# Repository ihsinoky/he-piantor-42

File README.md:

# HE Piantor 42

42-key Hall-effect keyboard targeting a unified reverse-V assembly. D-015
defines reusable Main + Left/Right Wings; future Wing geometry must be
project-owned or explicitly approved.

> [!WARNING]
> **Experimental hardware:** Main Rev.4, Matrix Rev.3, Wing Rev.3 and the final
> case data are design baselines. No PCB has completed physical validation,
> and this repository does
> not describe a production-ready keyboard. Do not order or manufacture from
> the current files without completing the documented review gates.

## Target

- 42 keys
- Piantor-derived column-staggered layout
- Unified reverse-V keyboard assembly; modular Main + Wings
- Evaluate 17.0 / 16.5 / 16.0 mm pitch; production pitch remains open
- Full-height Hall-effect magnetic switches
- USB-C wired only
- Vial-compatible keymap, 4 layers
- Dedicated power indicator LED
- Separate layer indicator LED
- JLCPCB PCBA target
- FDM-printable enclosure

## Development flow

The design baseline is Main Rev.4 / Matrix Rev.3 / Wing Rev.3 / final case data.
Start with the [current artifacts index](docs/artifacts-index.md) for CAD,
manufacturing packages, case exports and recorded verification.
[Project status](docs/project-status.md) is authoritative for outstanding gates:
Order 1 awaits PO GO, production pitch awaits Matrix measurements, and physical
validation is pending. The [dashboard](task/index.html) shows the milestone plan
and current position as a non-authoritative read model.

## Contribution status

Public release is completed, as recorded in
[`docs/public-release-readiness.md`](docs/public-release-readiness.md).
JITX physical-backend evaluation concluded NO-GO (D-016); it is historical,
not an unresolved current design gate. Prospective contributors should start
with an Issue and follow
[`docs/development-workflow.md`](docs/development-workflow.md); a green CI run
does not replace Product Owner approval.

## Licensing

This is a mixed-license repository:

- project-authored hardware, mechanical, and manufacturing designs use
  CERN-OHL-P-2.0;
- project-authored firmware, software, scripts, dashboard, and documentation
  use the MIT License; and
- third-party files retain their original licenses and notices.

See the authoritative [`LICENSE.md`](LICENSE.md) path map, the full texts under
[`LICENSES/`](LICENSES/), and the canonical
[third-party inventory](hardware/lib/THIRD_PARTY.md). Items marked **REVIEW
REQUIRED** are public-release blockers, not an assertion of ownership.

Public-release audit evidence and the current Human Gate result are documented
in [`docs/public-release-readiness.md`](docs/public-release-readiness.md). This
repository has completed public release; the hardware remains experimental and
is not production-ready.

設計の世代・過去の試行・証跡は [履歴索引](docs/history-index.md) を参照。

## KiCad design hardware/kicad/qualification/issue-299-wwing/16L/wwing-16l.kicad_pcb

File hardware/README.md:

# Hardware

現行は Main Rev.4／Matrix Rev.3／Wing Rev.3。CAD・回路源、単板とパネル、
ケース入力CSVは [成果物索引](../docs/artifacts-index.md) から正本へ進んでください。
Main は UDB C3 を別基板に持ち、左右Wingへ各200mmのハーネスで接続します。
Matrix は評価用18キー基板で、製品Wingとは別です。

設計採択と実機合格・発注GOは別です。[現行状態と残件](../docs/project-status.md)を参照。
`sensor-test/`、`main/`、旧Rev.M1やEDA評価の資料は設計履歴を含みます。

設計の世代・過去の試行・証跡は [履歴索引](../docs/history-index.md) を参照。

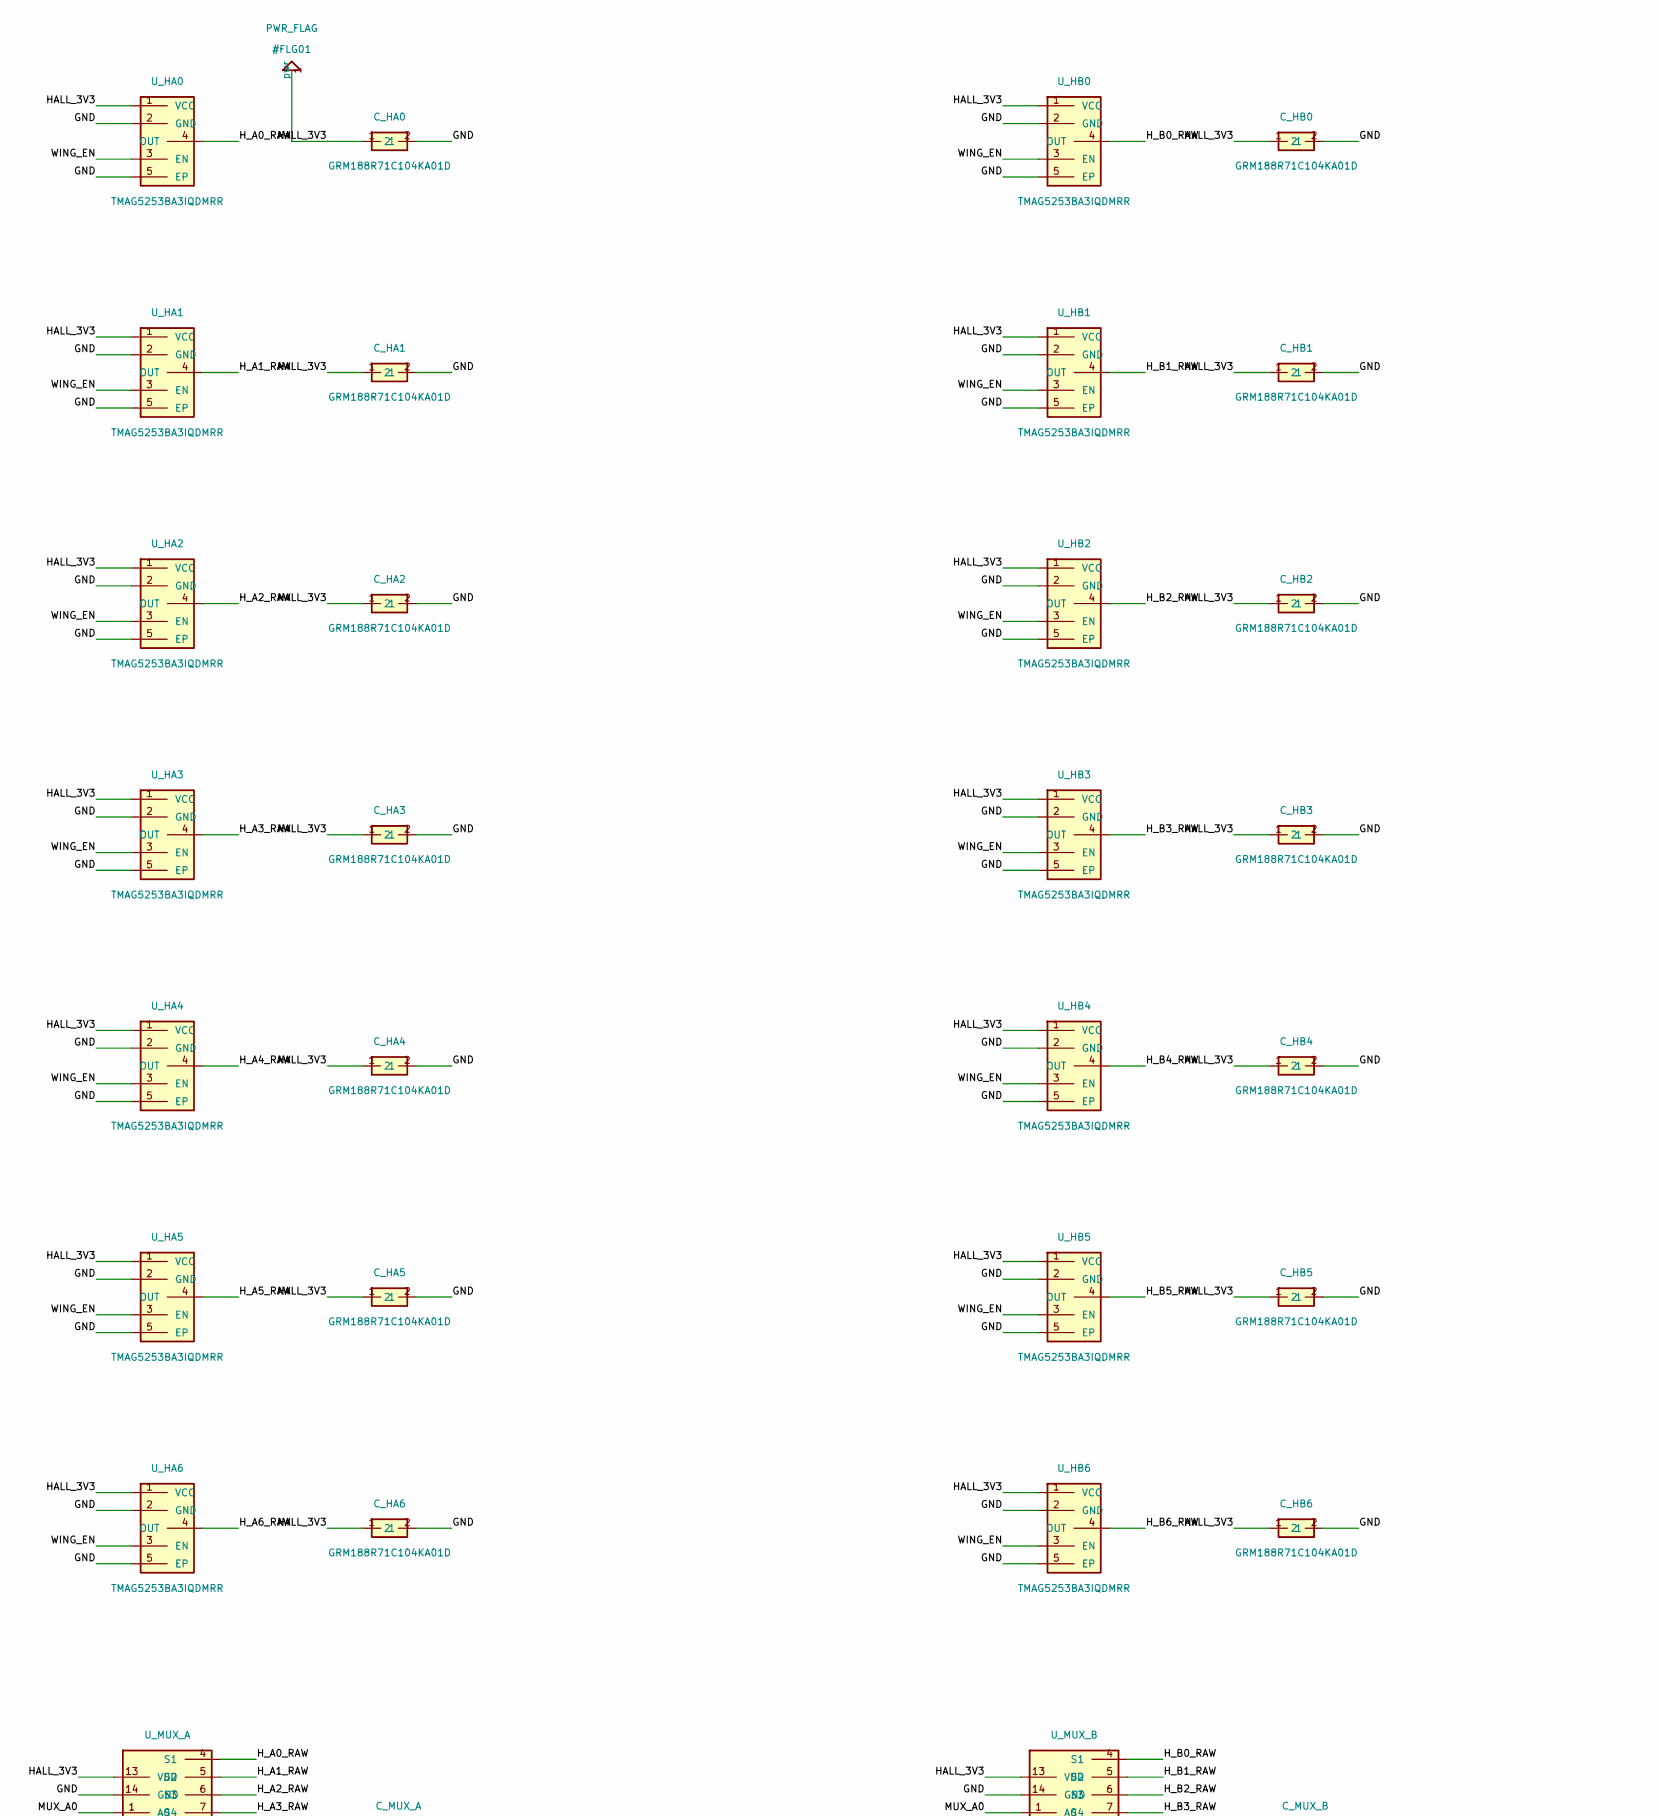
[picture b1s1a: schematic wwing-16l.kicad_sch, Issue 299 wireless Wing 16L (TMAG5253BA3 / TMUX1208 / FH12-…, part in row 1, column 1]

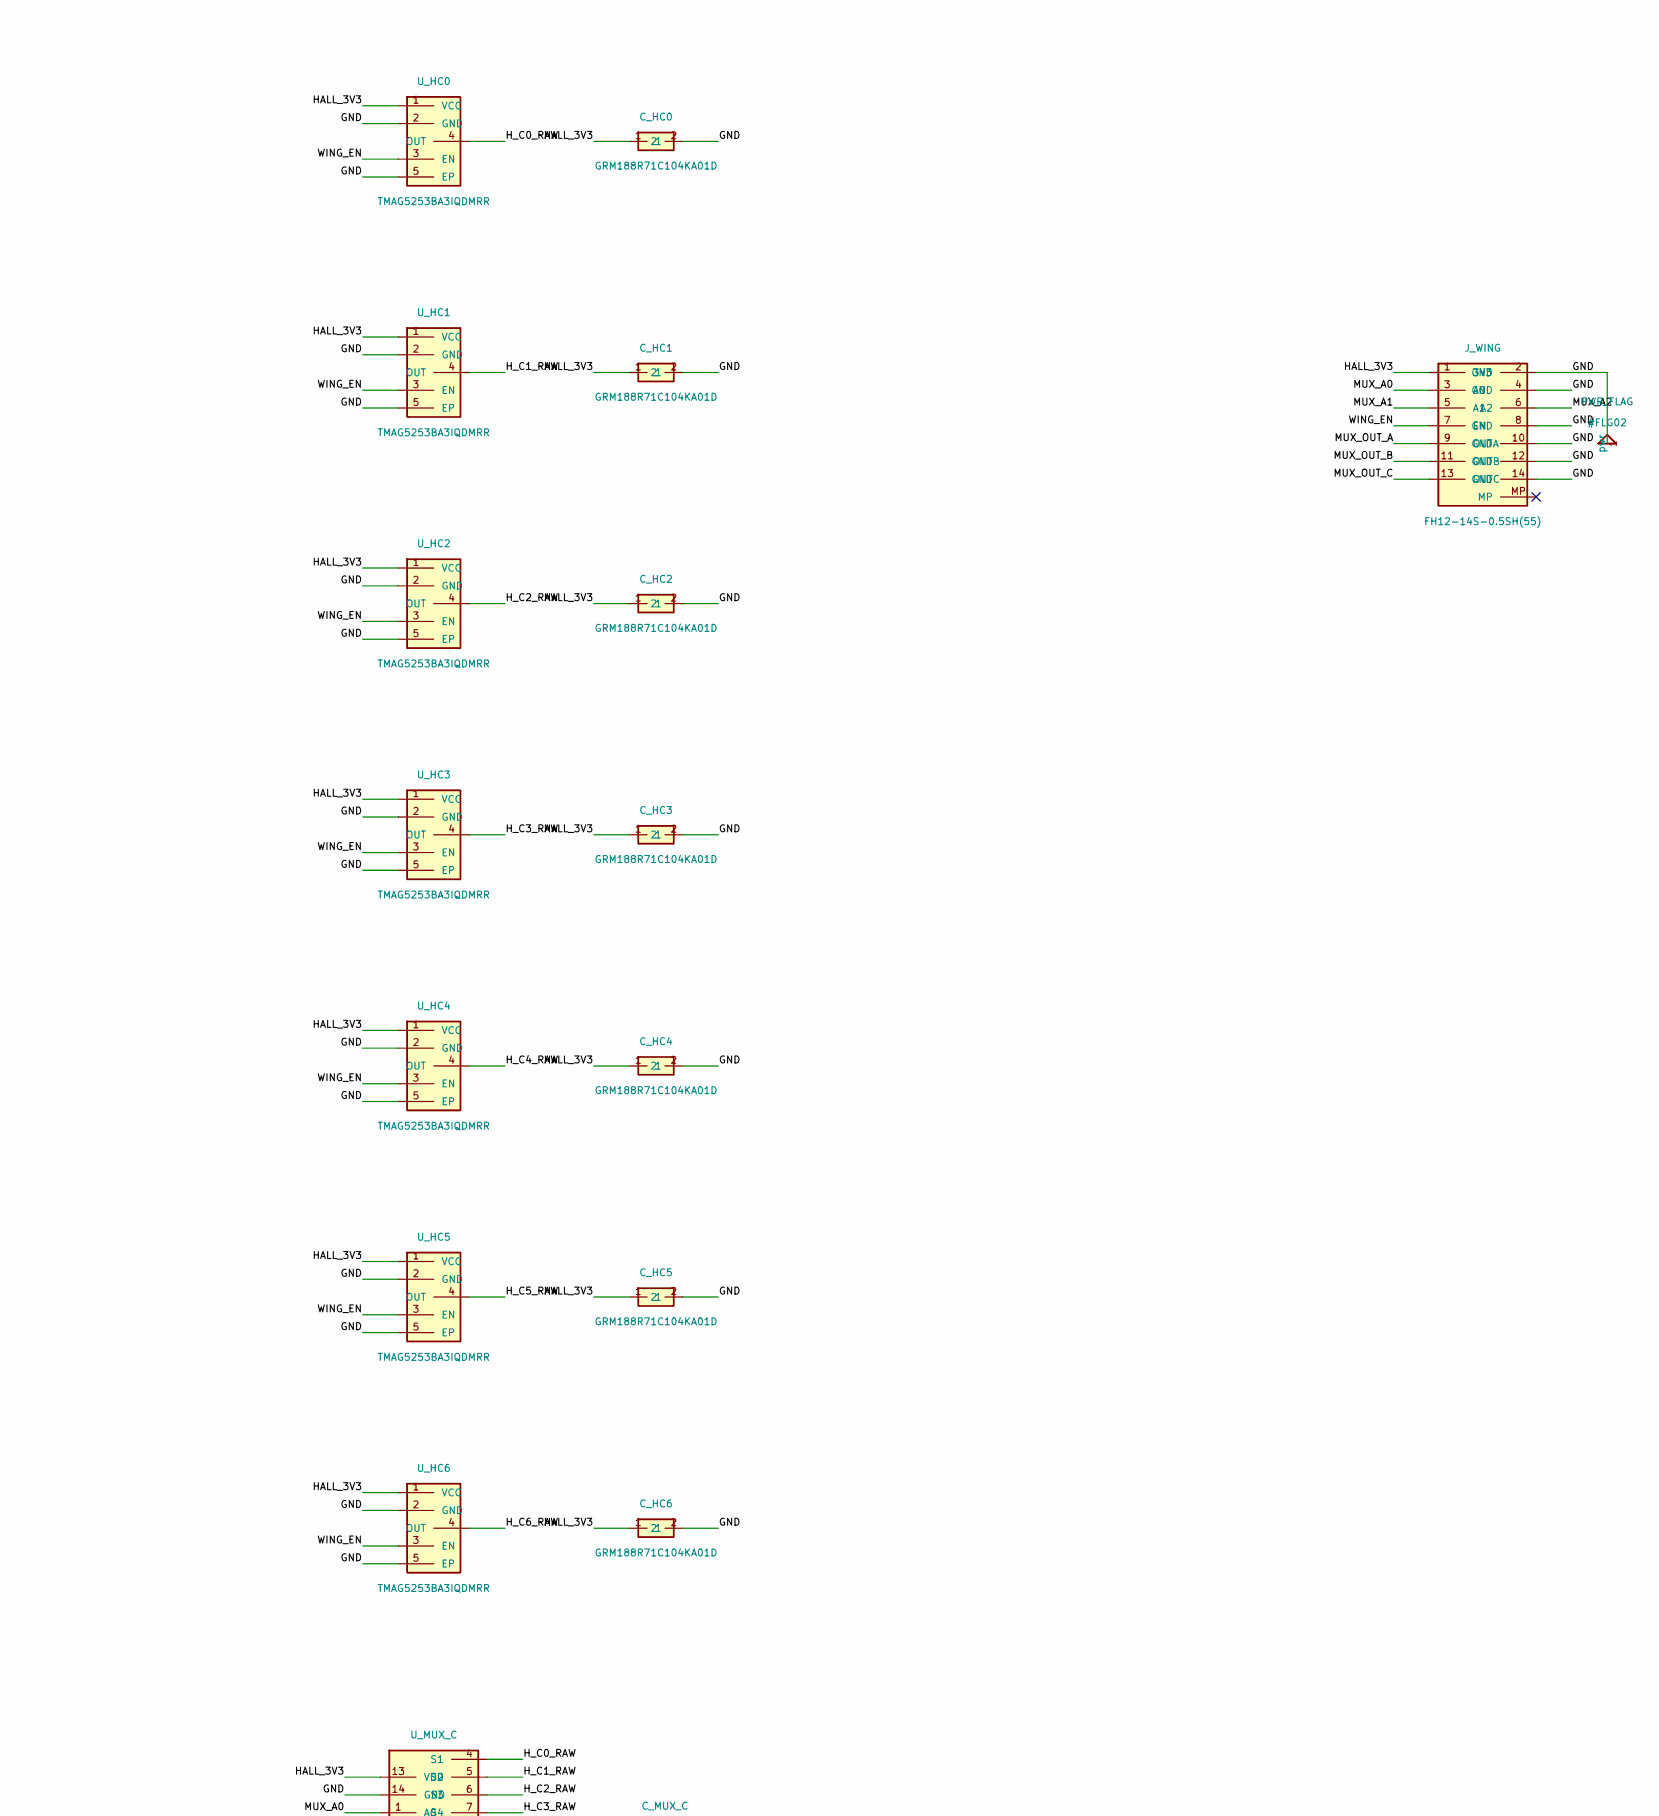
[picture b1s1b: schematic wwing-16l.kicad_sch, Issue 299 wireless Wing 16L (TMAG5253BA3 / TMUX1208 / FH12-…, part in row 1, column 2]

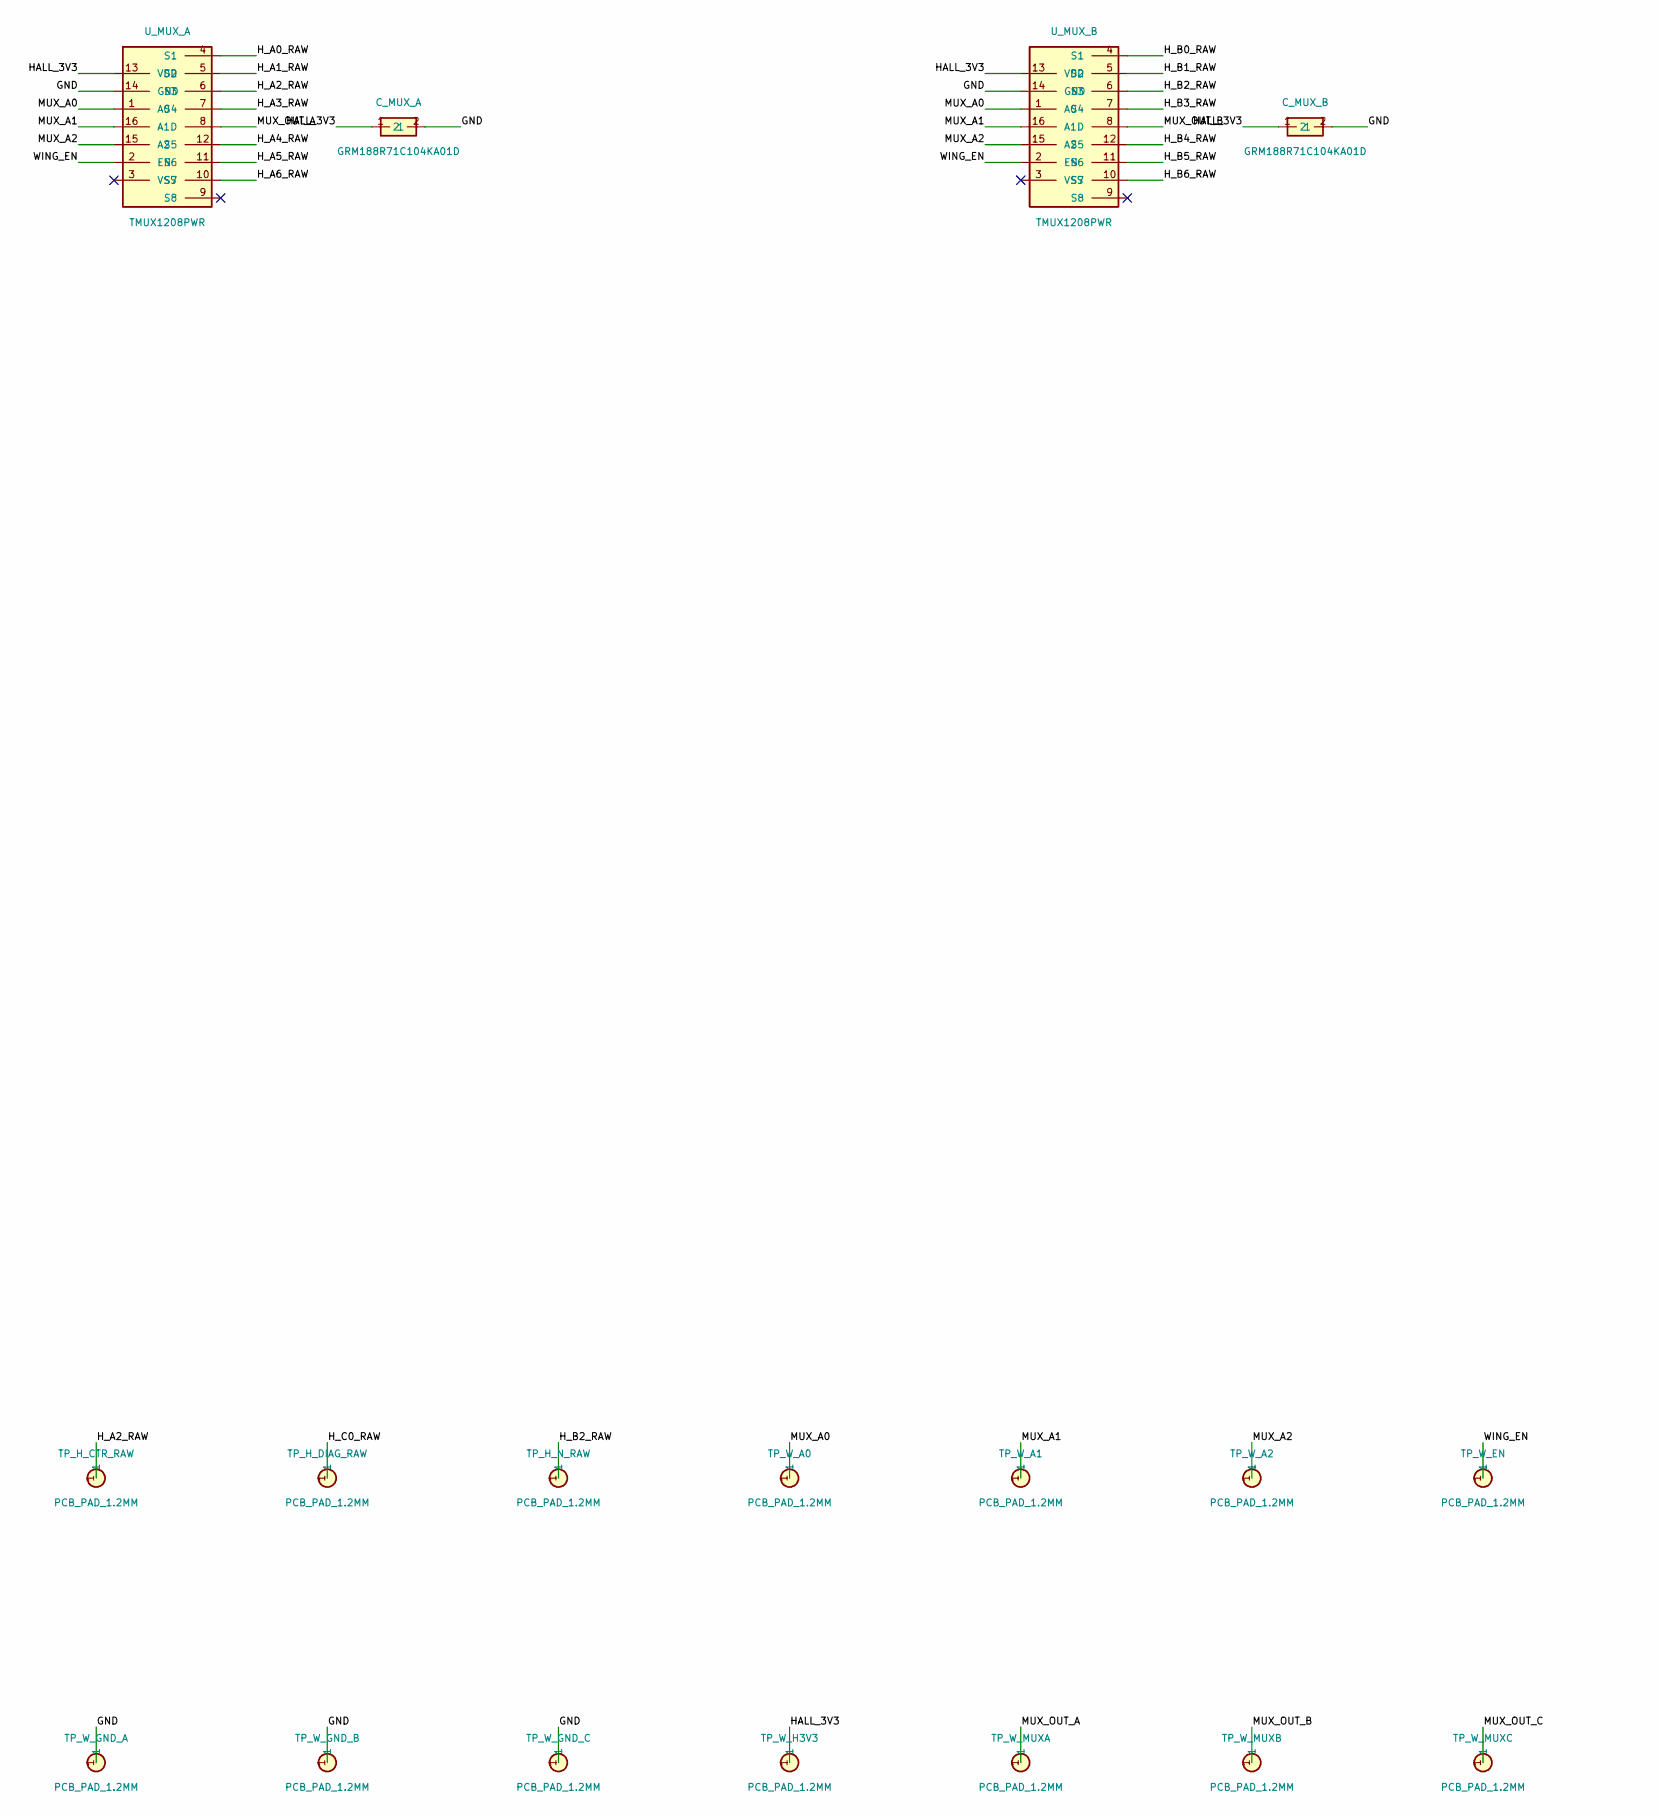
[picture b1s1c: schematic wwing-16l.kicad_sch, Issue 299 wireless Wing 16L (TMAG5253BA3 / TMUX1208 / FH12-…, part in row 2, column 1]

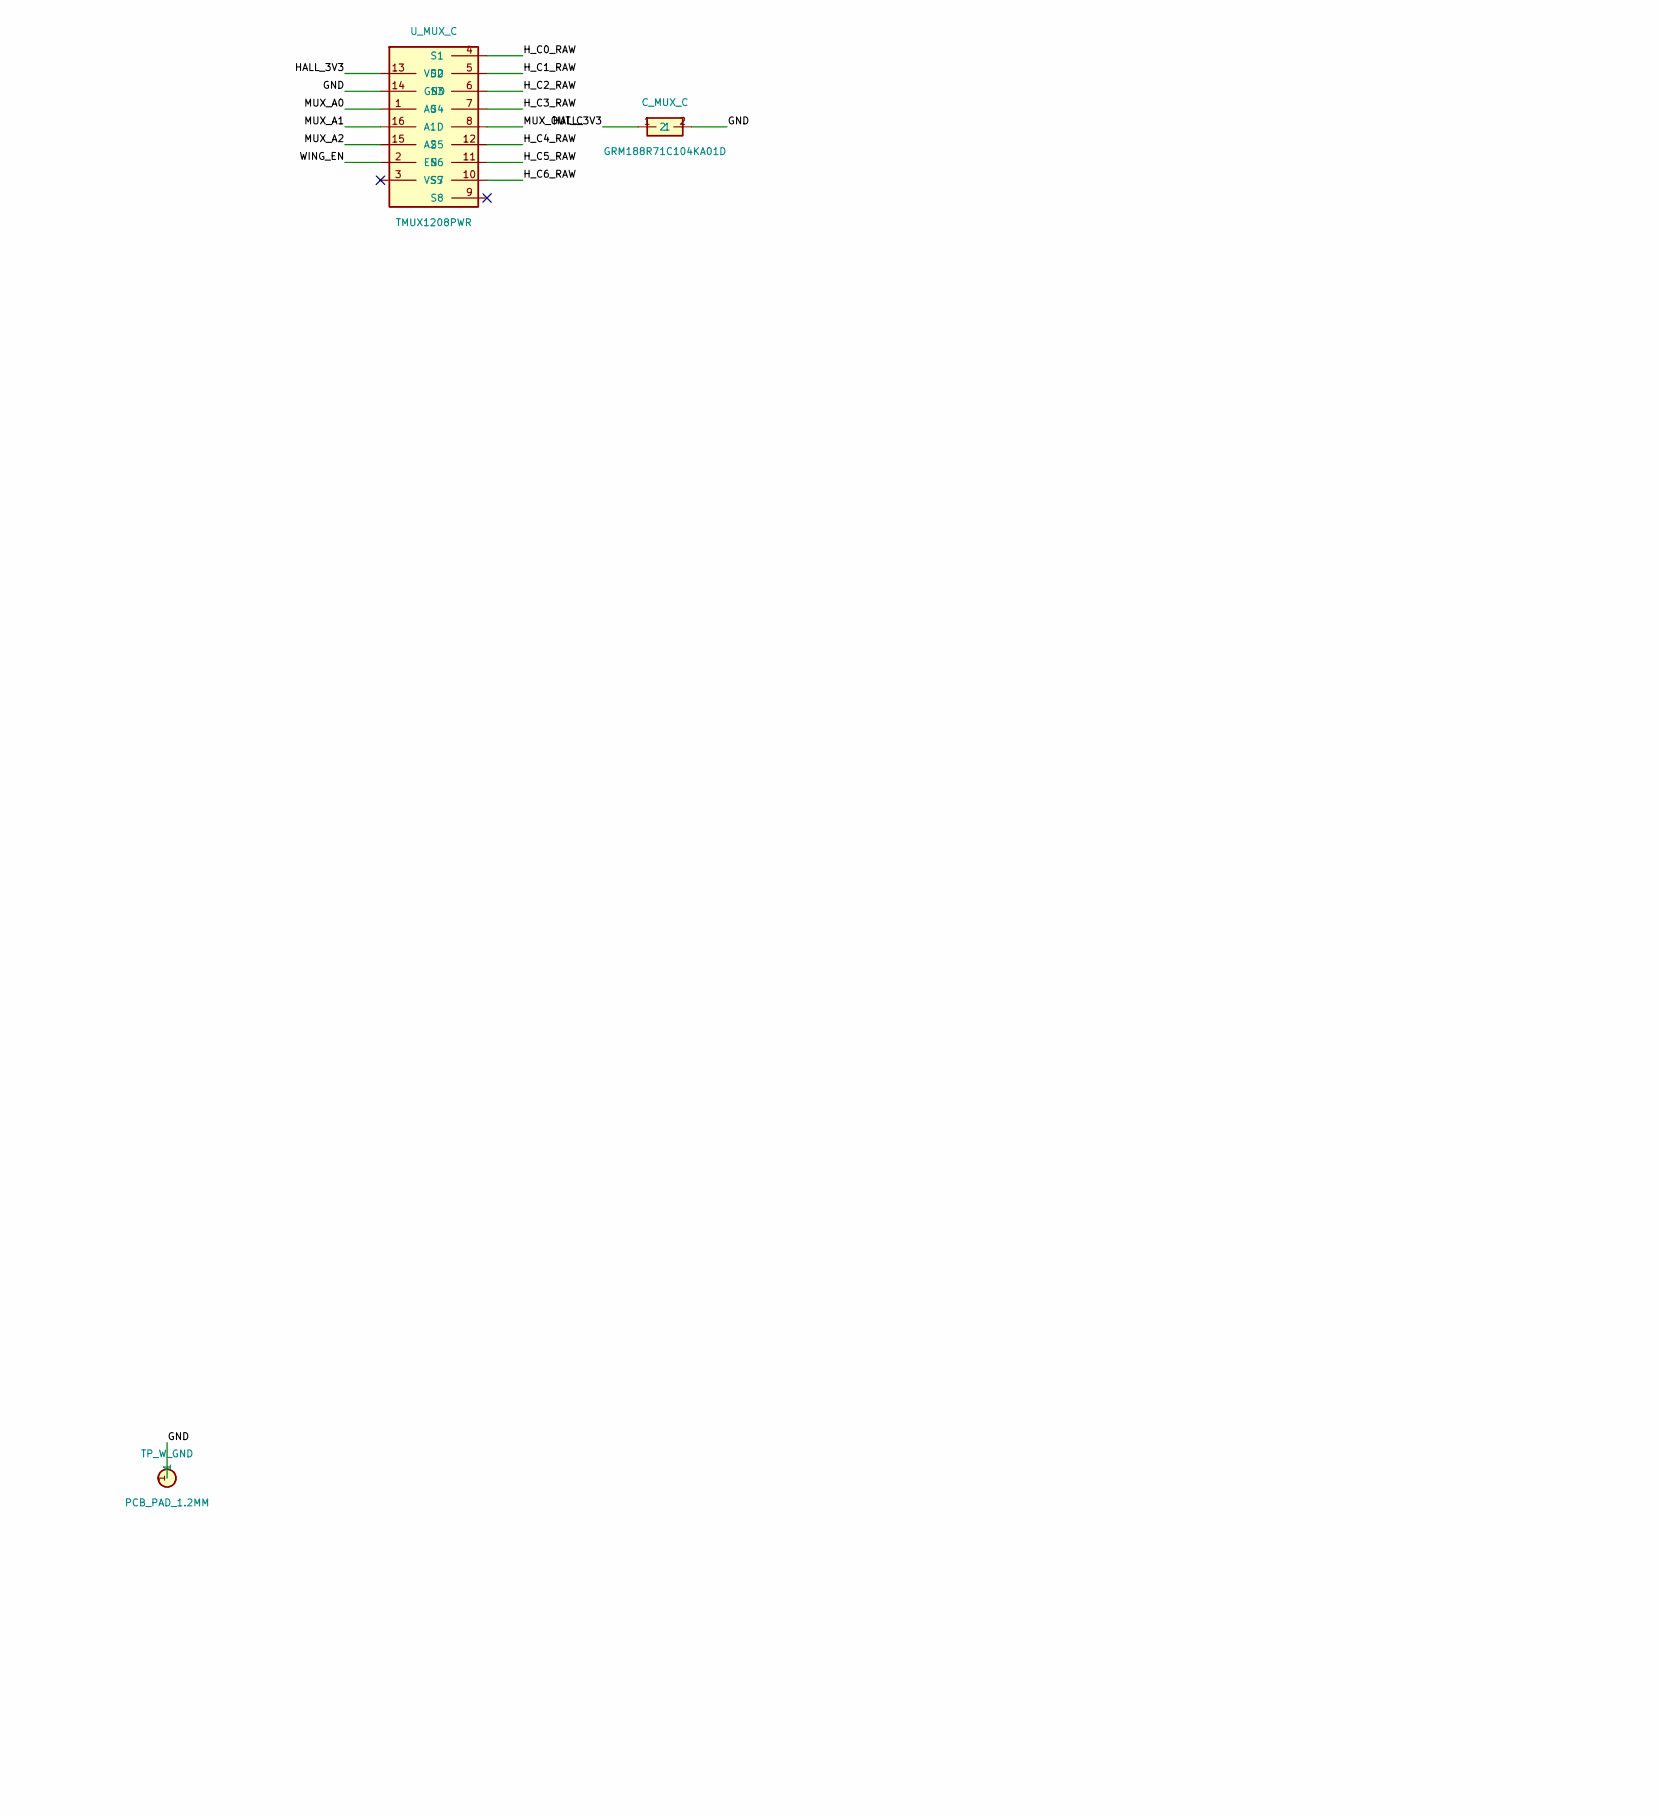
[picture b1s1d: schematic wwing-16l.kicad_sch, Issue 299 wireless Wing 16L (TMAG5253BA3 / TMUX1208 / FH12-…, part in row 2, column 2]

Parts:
C_HA0, C_HA1, C_HA2, C_HA3, C_HA4, C_HA5, C_HA6: GRM188R71C104KA01D; capacitor
C_HB0, C_HB1, C_HB2, C_HB3, C_HB4, C_HB5, C_HB6: GRM188R71C104KA01D; capacitor
C_HC0, C_HC1, C_HC2, C_HC3, C_HC4, C_HC5, C_HC6: GRM188R71C104KA01D; capacitor
C_MUX_A: GRM188R71C104KA01D; capacitor
C_MUX_B: GRM188R71C104KA01D; capacitor
C_MUX_C: GRM188R71C104KA01D; capacitor
J_WING: FH12-14S-0.5SH(55); Hirose_FH12-14S-0.5SH_1x14-1MP_P0.50mm_Horizontal
TP_H_CTR_RAW: PCB_PAD_1.2MM; testpoint
TP_H_DIAG_RAW: PCB_PAD_1.2MM; testpoint
TP_H_N_RAW: PCB_PAD_1.2MM; testpoint
TP_W_A0, TP_W_A1, TP_W_A2: PCB_PAD_1.2MM; testpoint
TP_W_EN: PCB_PAD_1.2MM; testpoint
TP_W_GND: PCB_PAD_1.2MM; testpoint
TP_W_GND_A: PCB_PAD_1.2MM; testpoint
TP_W_GND_B: PCB_PAD_1.2MM; testpoint
TP_W_GND_C: PCB_PAD_1.2MM; testpoint
TP_W_H3V3: PCB_PAD_1.2MM; testpoint
TP_W_MUXA: PCB_PAD_1.2MM; testpoint
TP_W_MUXB: PCB_PAD_1.2MM; testpoint
TP_W_MUXC: PCB_PAD_1.2MM; testpoint
U_HA0, U_HA1, U_HA2, U_HA3, U_HA4, U_HA5, U_HA6: TMAG5253BA3IQDMRR; TMAG5253BA3_X2SON-4
U_HB0, U_HB1, U_HB2, U_HB3, U_HB4, U_HB5, U_HB6: TMAG5253BA3IQDMRR; TMAG5253BA3_X2SON-4
U_HC0, U_HC1, U_HC2, U_HC3, U_HC4, U_HC5, U_HC6: TMAG5253BA3IQDMRR; TMAG5253BA3_X2SON-4
U_MUX_A: TMUX1208PWR; mux
U_MUX_B: TMUX1208PWR; mux
U_MUX_C: TMUX1208PWR; mux

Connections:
GND: C_HA0.2, C_HA1.2, C_HA2.2, C_HA3.2, C_HA4.2, C_HA5.2, C_HA6.2, C_HB0.2, C_HB1.2, C_HB2.2, C_HB3.2, C_HB4.2, C_HB5.2, C_HB6.2, C_HC0.2, C_HC1.2, C_HC2.2, C_HC3.2, C_HC4.2, C_HC5.2, C_HC6.2, C_MUX_A.2, C_MUX_B.2, C_MUX_C.2, J_WING.2 (GND), J_WING.4 (GND), J_WING.8 (GND), J_WING.10 (GND), J_WING.12 (GND), J_WING.14 (GND), TP_W_GND.1, TP_W_GND_A.1, TP_W_GND_B.1, TP_W_GND_C.1, U_HA0.2 (GND), U_HA0.5 (EP), U_HA1.2 (GND), U_HA1.5 (EP), U_HA2.2 (GND), U_HA2.5 (EP), U_HA3.2 (GND), U_HA3.5 (EP), U_HA4.2 (GND), U_HA4.5 (EP), U_HA5.2 (GND), U_HA5.5 (EP), U_HA6.2 (GND), U_HA6.5 (EP), U_HB0.2 (GND), U_HB0.5 (EP), U_HB1.2 (GND), U_HB1.5 (EP), U_HB2.2 (GND), U_HB2.5 (EP), U_HB3.2 (GND), U_HB3.5 (EP), U_HB4.2 (GND), U_HB4.5 (EP), U_HB5.2 (GND), U_HB5.5 (EP), U_HB6.2 (GND), U_HB6.5 (EP), U_HC0.2 (GND), U_HC0.5 (EP), U_HC1.2 (GND), U_HC1.5 (EP), U_HC2.2 (GND), U_HC2.5 (EP), U_HC3.2 (GND), U_HC3.5 (EP), U_HC4.2 (GND), U_HC4.5 (EP), U_HC5.2 (GND), U_HC5.5 (EP), U_HC6.2 (GND), U_HC6.5 (EP), U_MUX_A.14 (GND), U_MUX_B.14 (GND), U_MUX_C.14 (GND)
HALL_3V3: C_HA0.1, C_HA1.1, C_HA2.1, C_HA3.1, C_HA4.1, C_HA5.1, C_HA6.1, C_HB0.1, C_HB1.1, C_HB2.1, C_HB3.1, C_HB4.1, C_HB5.1, C_HB6.1, C_HC0.1, C_HC1.1, C_HC2.1, C_HC3.1, C_HC4.1, C_HC5.1, C_HC6.1, C_MUX_A.1, C_MUX_B.1, C_MUX_C.1, J_WING.1 (3V3), TP_W_H3V3.1, U_HA0.1 (VCC), U_HA1.1 (VCC), U_HA2.1 (VCC), U_HA3.1 (VCC), U_HA4.1 (VCC), U_HA5.1 (VCC), U_HA6.1 (VCC), U_HB0.1 (VCC), U_HB1.1 (VCC), U_HB2.1 (VCC), U_HB3.1 (VCC), U_HB4.1 (VCC), U_HB5.1 (VCC), U_HB6.1 (VCC), U_HC0.1 (VCC), U_HC1.1 (VCC), U_HC2.1 (VCC), U_HC3.1 (VCC), U_HC4.1 (VCC), U_HC5.1 (VCC), U_HC6.1 (VCC), U_MUX_A.13 (VDD), U_MUX_B.13 (VDD), U_MUX_C.13 (VDD)
H_A0_RAW: U_HA0.4 (OUT), U_MUX_A.4 (S1)
H_A1_RAW: U_HA1.4 (OUT), U_MUX_A.5 (S2)
H_A2_RAW: TP_H_CTR_RAW.1, U_HA2.4 (OUT), U_MUX_A.6 (S3)
H_A3_RAW: U_HA3.4 (OUT), U_MUX_A.7 (S4)
H_A4_RAW: U_HA4.4 (OUT), U_MUX_A.12 (S5)
H_A5_RAW: U_HA5.4 (OUT), U_MUX_A.11 (S6)
H_A6_RAW: U_HA6.4 (OUT), U_MUX_A.10 (S7)
H_B0_RAW: U_HB0.4 (OUT), U_MUX_B.4 (S1)
H_B1_RAW: U_HB1.4 (OUT), U_MUX_B.5 (S2)
H_B2_RAW: TP_H_N_RAW.1, U_HB2.4 (OUT), U_MUX_B.6 (S3)
H_B3_RAW: U_HB3.4 (OUT), U_MUX_B.7 (S4)
H_B4_RAW: U_HB4.4 (OUT), U_MUX_B.12 (S5)
H_B5_RAW: U_HB5.4 (OUT), U_MUX_B.11 (S6)
H_B6_RAW: U_HB6.4 (OUT), U_MUX_B.10 (S7)
H_C0_RAW: TP_H_DIAG_RAW.1, U_HC0.4 (OUT), U_MUX_C.4 (S1)
H_C1_RAW: U_HC1.4 (OUT), U_MUX_C.5 (S2)
H_C2_RAW: U_HC2.4 (OUT), U_MUX_C.6 (S3)
H_C3_RAW: U_HC3.4 (OUT), U_MUX_C.7 (S4)
H_C4_RAW: U_HC4.4 (OUT), U_MUX_C.12 (S5)
H_C5_RAW: U_HC5.4 (OUT), U_MUX_C.11 (S6)
H_C6_RAW: U_HC6.4 (OUT), U_MUX_C.10 (S7)
MUX_A0: J_WING.3 (A0), TP_W_A0.1, U_MUX_A.1 (A0), U_MUX_B.1 (A0), U_MUX_C.1 (A0)
MUX_A1: J_WING.5 (A1), TP_W_A1.1, U_MUX_A.16 (A1), U_MUX_B.16 (A1), U_MUX_C.16 (A1)
MUX_A2: J_WING.6 (A2), TP_W_A2.1, U_MUX_A.15 (A2), U_MUX_B.15 (A2), U_MUX_C.15 (A2)
MUX_OUT_A: J_WING.9 (OUTA), TP_W_MUXA.1, U_MUX_A.8 (D)
MUX_OUT_B: J_WING.11 (OUTB), TP_W_MUXB.1, U_MUX_B.8 (D)
MUX_OUT_C: J_WING.13 (OUTC), TP_W_MUXC.1, U_MUX_C.8 (D)
WING_EN: J_WING.7 (EN), TP_W_EN.1, U_HA0.3 (EN), U_HA1.3 (EN), U_HA2.3 (EN), U_HA3.3 (EN), U_HA4.3 (EN), U_HA5.3 (EN), U_HA6.3 (EN), U_HB0.3 (EN), U_HB1.3 (EN), U_HB2.3 (EN), U_HB3.3 (EN), U_HB4.3 (EN), U_HB5.3 (EN), U_HB6.3 (EN), U_HC0.3 (EN), U_HC1.3 (EN), U_HC2.3 (EN), U_HC3.3 (EN), U_HC4.3 (EN), U_HC5.3 (EN), U_HC6.3 (EN), U_MUX_A.2 (EN), U_MUX_B.2 (EN), U_MUX_C.2 (EN)

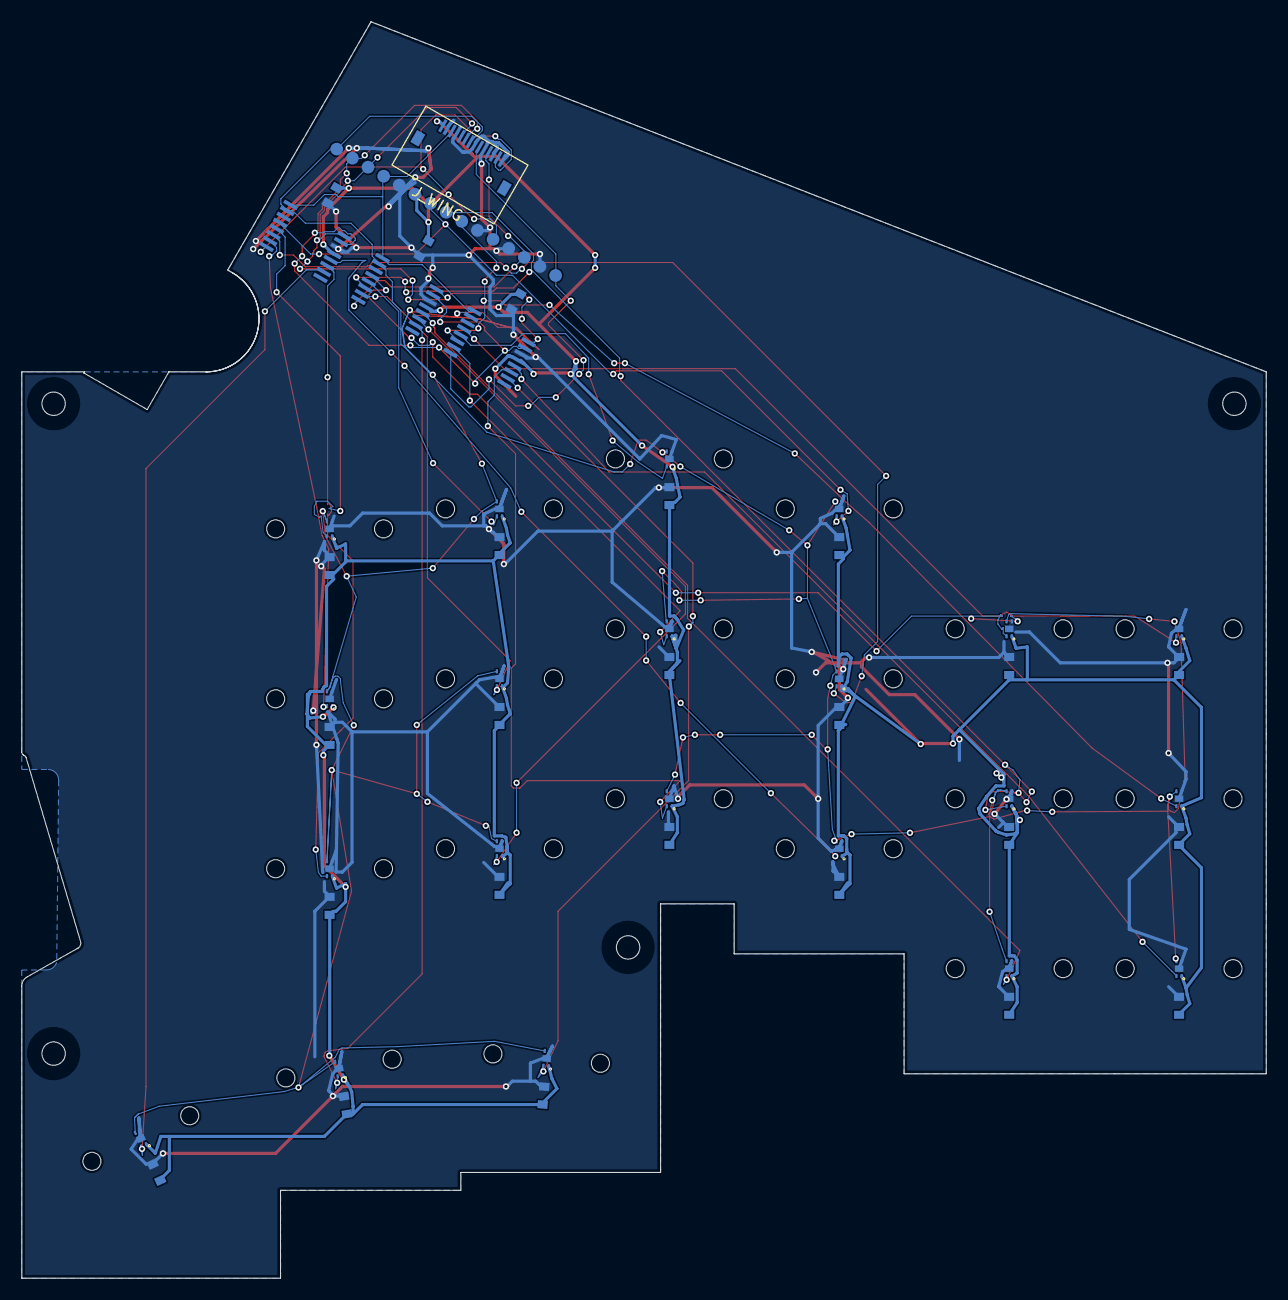
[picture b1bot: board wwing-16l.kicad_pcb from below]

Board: 2 copper layers, 117.2 x 118.3 mm, 110 parts (64 on the bottom side), 30 nets.

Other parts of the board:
H1, H2, H3, H4: NPTH_2.2; NPTH
MH_1_1, MH_1_2, MH_2_1, MH_2_2, MH_3_1, MH_3_2, MH_4_1, MH_4_2, MH_5_1, MH_5_2, MH_6_1, MH_6_2, MH_7_1, MH_7_2, MH_8_1, MH_8_2, MH_9_1, MH_9_2, MH_10_1, MH_10_2, MH_11_1, MH_11_2, MH_12_1, MH_12_2, MH_13_1, MH_13_2, MH_14_1, MH_14_2, MH_15_1, MH_15_2, MH_16_1, MH_16_2, MH_17_1, MH_17_2, MH_18_1, MH_18_2, MH_19_1, MH_19_2, MH_20_1, MH_20_2, MH_21_1, MH_21_2: NPTH_1.7; NPTH

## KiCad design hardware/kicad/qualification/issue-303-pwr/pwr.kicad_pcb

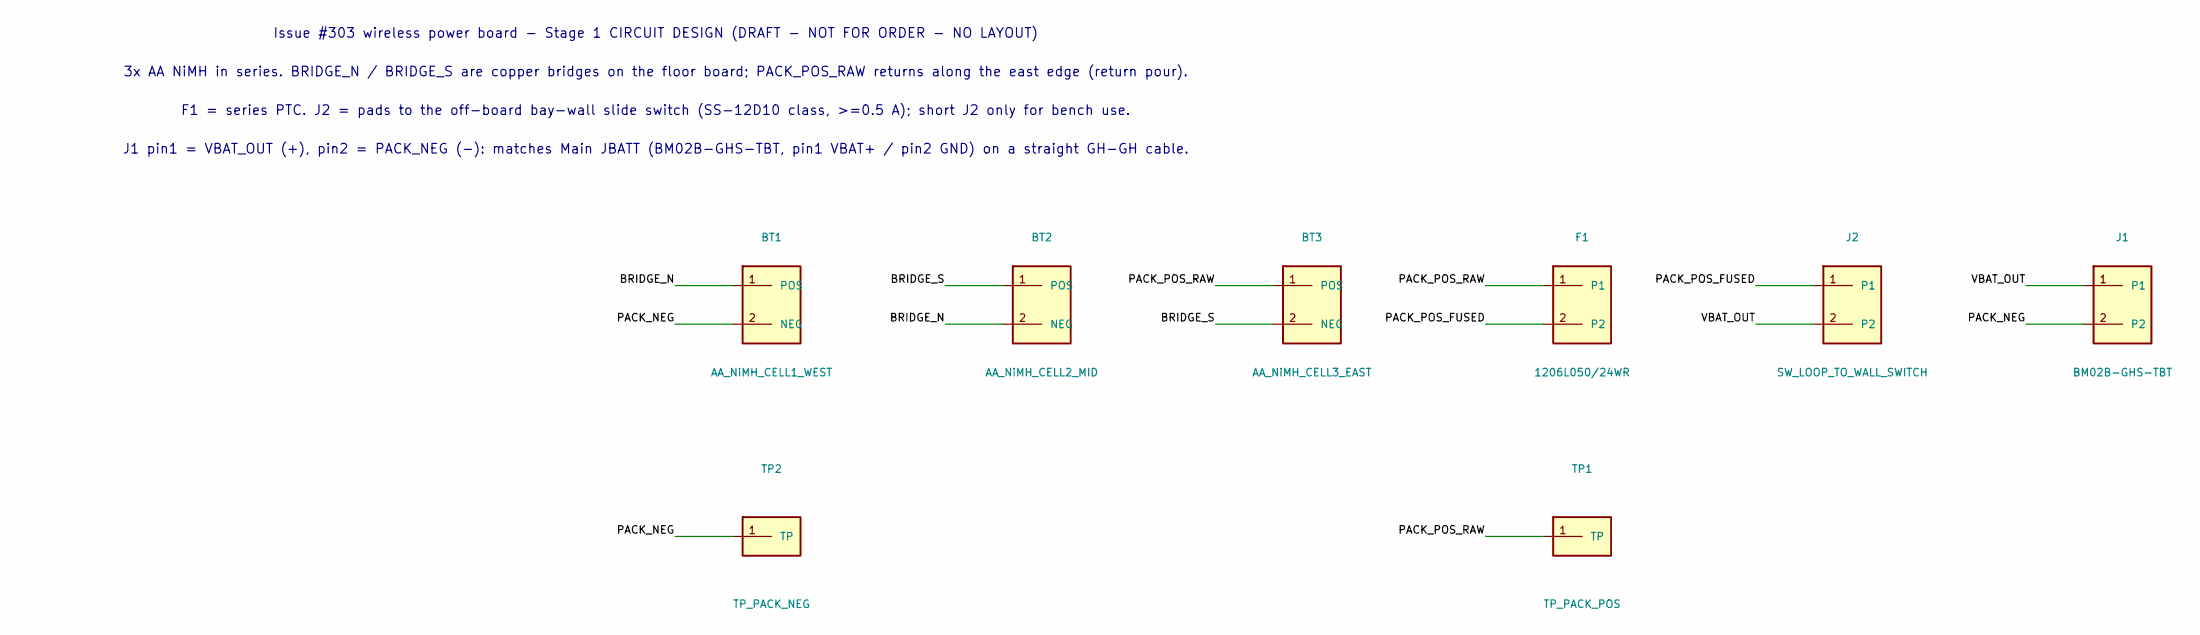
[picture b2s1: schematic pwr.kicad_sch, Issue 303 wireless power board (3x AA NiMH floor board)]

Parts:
BT1: AA_NiMH_CELL1_WEST
BT2: AA_NiMH_CELL2_MID
BT3: AA_NiMH_CELL3_EAST
F1: 1206L050/24WR
J1: BM02B-GHS-TBT
J2: SW_LOOP_TO_WALL_SWITCH
TP1: TP_PACK_POS
TP2: TP_PACK_NEG

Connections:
BRIDGE_N: BT1.1 (POS), BT2.2 (NEG)
BRIDGE_S: BT2.1 (POS), BT3.2 (NEG)
PACK_NEG: BT1.2 (NEG), J1.2, TP2.1
PACK_POS_FUSED: F1.2, J2.1
PACK_POS_RAW: BT3.1 (POS), F1.1, TP1.1
VBAT_OUT: J1.1, J2.2

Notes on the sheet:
Issue #303 wireless power board - Stage 1 CIRCUIT DESIGN (DRAFT - NOT FOR ORDER - NO LAYOUT)
3x AA NiMH in series. BRIDGE_N / BRIDGE_S are copper bridges on the floor board; PACK_POS_RAW returns along the east edge (return pour).
F1 = series PTC. J2 = pads to the off-board bay-wall slide switch (SS-12D10 class, >=0.5 A); short J2 only for bench use.
J1 pin1 = VBAT_OUT (+), pin2 = PACK_NEG (-): matches Main JBATT (BM02B-GHS-TBT, pin1 VBAT+ / pin2 GND) on a straight GH-GH cable.

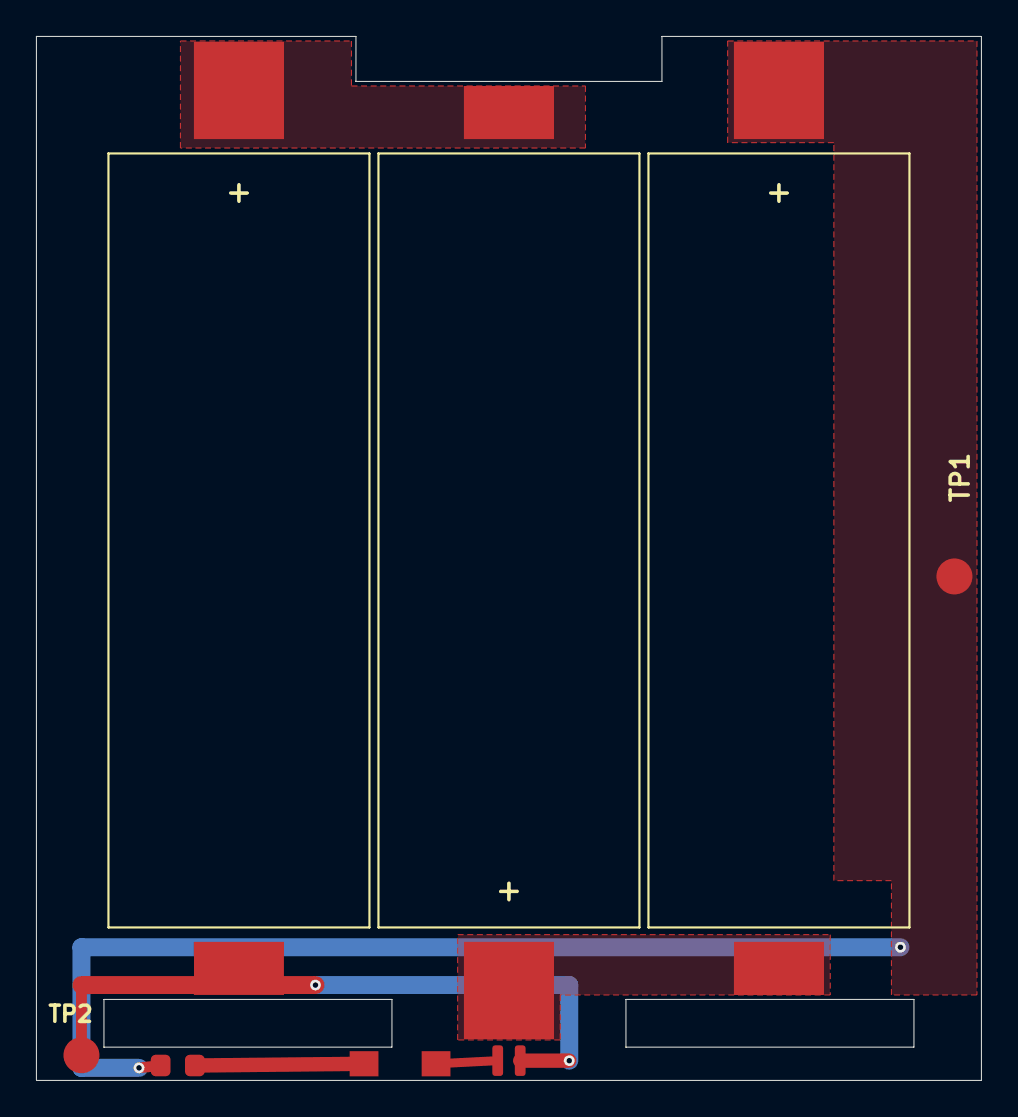
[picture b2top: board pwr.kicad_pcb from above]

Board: 2 copper layers, 52.5 x 58.0 mm, 8 parts (0 on the bottom side), 6 nets.
